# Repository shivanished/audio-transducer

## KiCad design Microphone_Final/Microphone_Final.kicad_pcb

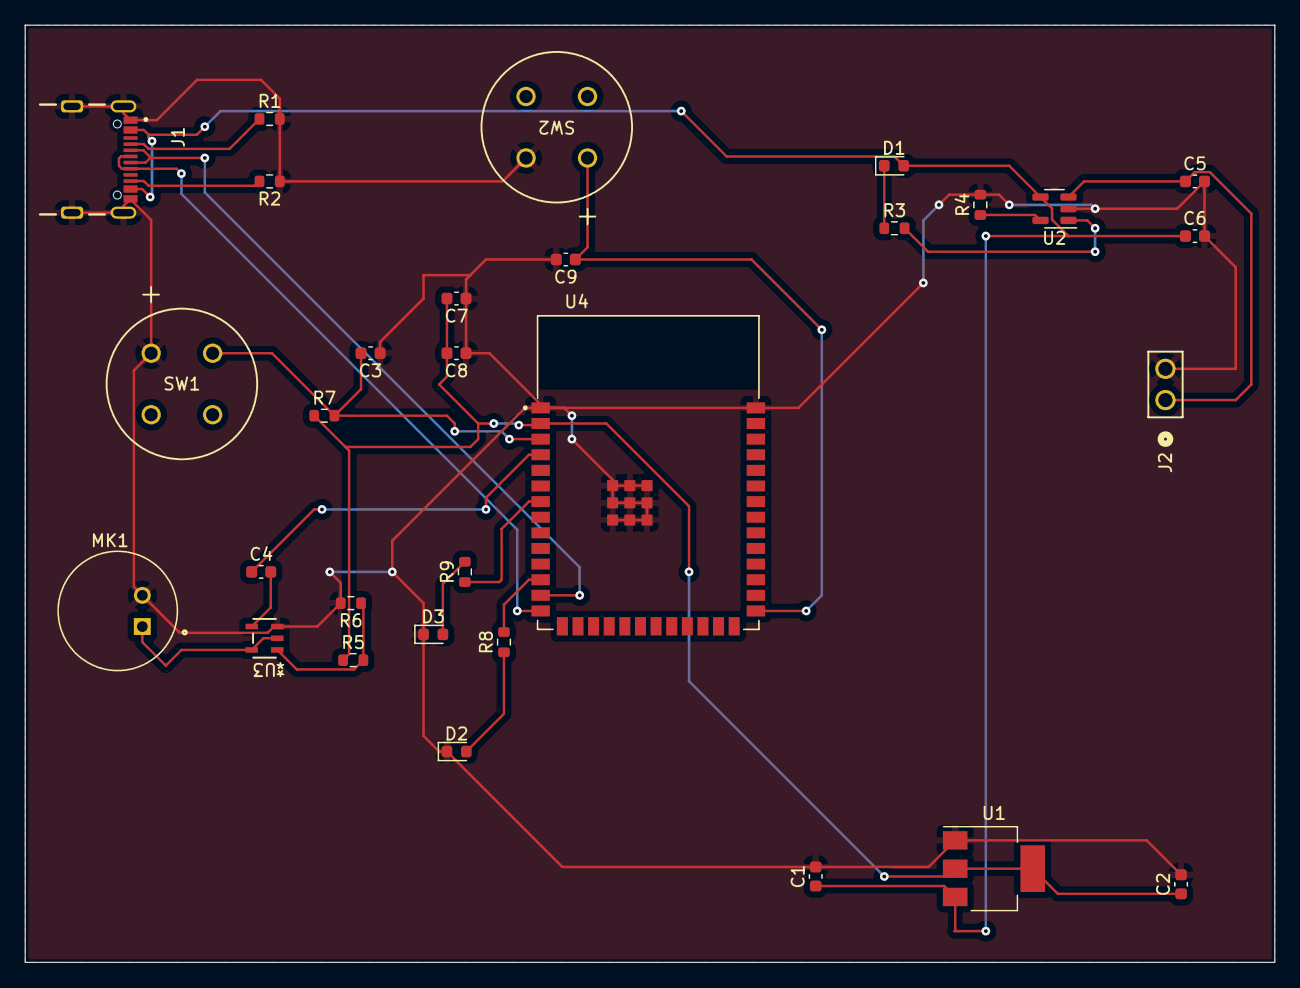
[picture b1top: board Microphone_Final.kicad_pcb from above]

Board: 2 copper layers, 101.6 x 76.2 mm, 30 parts (0 on the bottom side), 21 nets.

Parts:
C1: 100nF; C_0603_1608Metric
C2: 10uF; C_0603_1608Metric
C3, C8, C9: .1uF; C_0603_1608Metric
C4: 1 uF; C_0603_1608Metric
C5, C6: 4.7 uF; C_0603_1608Metric
C7: 1uF; C_0603_1608Metric
D1, D2, D3: LED; LED_0603_1608Metric
J1: USB_C_Receptacle_USB2.0; GCT_USB4105-GF-A
J2: Conn_01x02_Pin; CONN_61300211121_WRE
MK1: Microphone; MIC_CMA-4544PF-W
R1, R2: 5.1 k; R_0603_1608Metric
R3, R8, R9: 470; R_0603_1608Metric
R4: 2000; R_0603_1608Metric
R5: 100; R_0603_1608Metric
R6: 1k; R_0603_1608Metric
R7: 10k; R_0603_1608Metric
SW1: Reset; D6R90_CNK
SW2: Boot; D6R90_CNK
U1: LD1117S33TR_SOT223; SOT-223-3_TabPin2
U2: MCP73831-2-OT; SOT-23-5
U3: ${SIM.PARAMS}; SOT-23-5_MC_MCH-L
U4: ESP32-S2-SOLO; XCVR_ESP32-S2-SOLO-N4

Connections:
+3.3V: C2.1, C7.2, C8.2, R5.1, R7.1, U1.2 (VO), U4.2 (3V3)
+5V: C1.1, C6.1, D1.2 (A), J1.A4_B9, J1.B4_A9, U1.3 (VI), U2.4 (V_{DD})
+BATT: C5.1, J2.1, U2.3 (V_{BAT})
/D+: J1.A6 (D+), J1.B6 (D+), U4.14 (GPIO20/U1CTS/ADC2_CH9/CLK_OUT1/USB_D+)
/D-: J1.A7 (D-), J1.B7 (D-), U4.13 (GPIO19/U1RTS/ADC2_CH8/CLK_OUT2/USB_D-)
GND: C1.2, C2.2, C3.1, C5.2, C6.2, C7.1, C8.1, C9.2, D2.1 (K), D3.1 (K), J1.A1_B12, J1.B1_A12, J1.SH1, J1.SH2, J1.SH3, J1.SH4, J2.2, MK1.2 (+), R1.2, R2.1, R4.2, R6.2, SW1.1, SW2.2, U1.1 (GND), U2.2 (V_{SS}), U3.3 (V+), U4.1 (GND), U4.40 (GND), U4.41_1, U4.41_2, U4.41_3, U4.41_4, U4.41_5, U4.41_6, U4.41_7, U4.41_8, U4.41_9
unnamed: D1.1 (K), R3.1
unnamed: D2.2 (A), R8.1
unnamed: D3.2 (A), R9.2
unnamed: J1.A5 (CC1), R1.1
unnamed: J1.B5 (CC2), R2.2
unnamed: MK1.1 (-), U3.2 (-), U3.5
unnamed: R4.1, U2.5 (PROG)
unnamed: R3.2, U2.1 (STAT)
unnamed: R5.2, R6.1, U3.1 (+)
unnamed: C4.2, U3.4 (V-)
unnamed: C3.2, R7.2, SW1.2, U4.3 (EN)
unnamed: C9.1, SW2.1, U4.27 (GPIO0)
unnamed: C4.1, U4.4 (GPIO4/TOUCH4/ADC1_CH3)
unnamed: R9.1, U4.7 (GPIO7/TOUCH7/ADC1_CH6)
unnamed: R8.2, U4.12 (GPIO8/TOUCH8/ADC1_CH7)

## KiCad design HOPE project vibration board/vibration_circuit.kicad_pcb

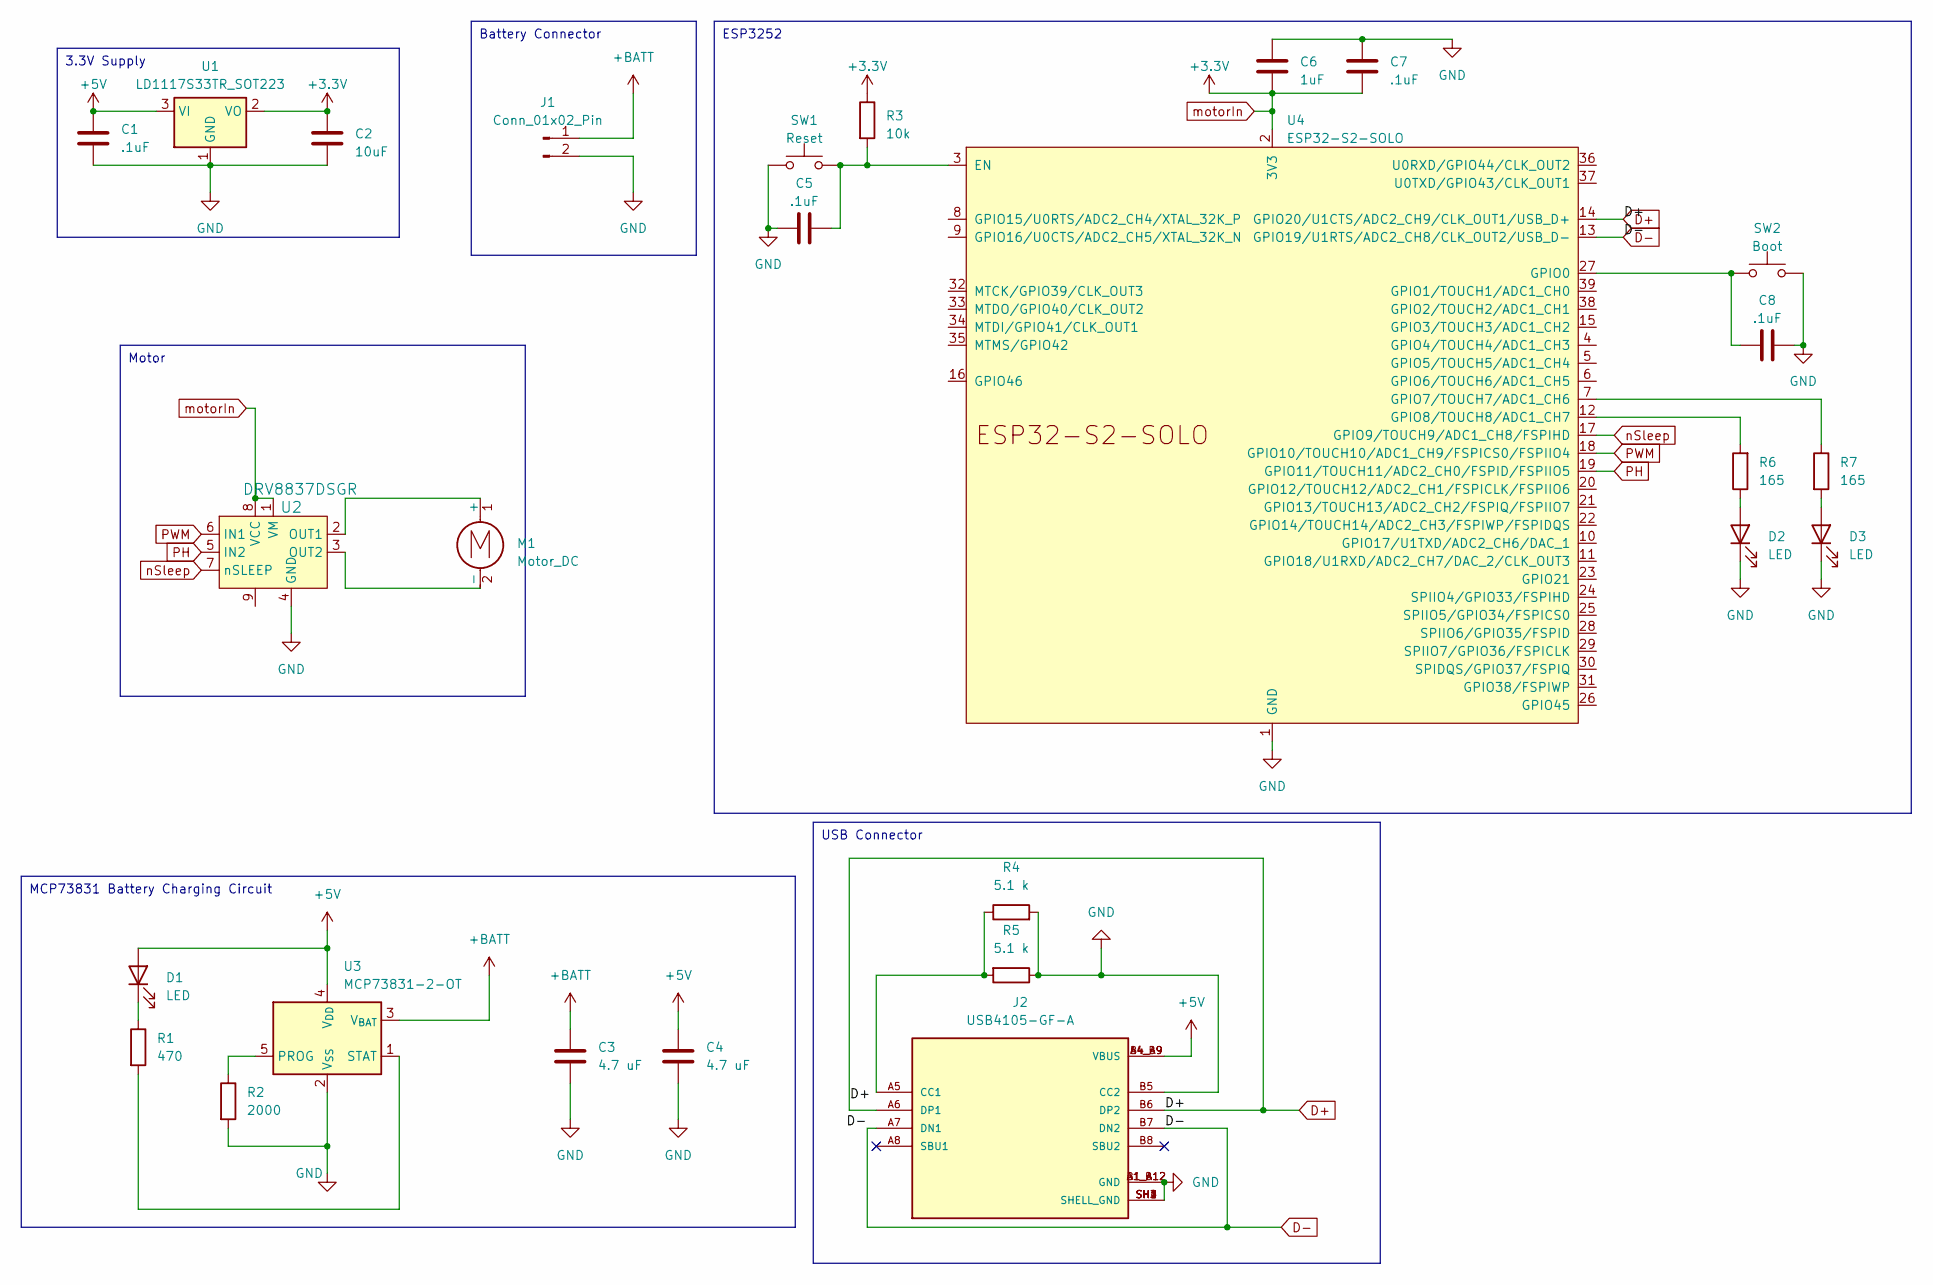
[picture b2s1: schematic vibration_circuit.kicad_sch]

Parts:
C1, C5, C7, C8: .1uF; C_0603_1608Metric
C2: 10uF; C_0603_1608Metric
C3, C4: 4.7 uF; C_0603_1608Metric
C6: 1uF; C_0603_1608Metric
D1, D2, D3: LED; LED_0603_1608Metric
J1: Conn_01x02_Pin; PinSocket_1x02_P2.54mm_Vertical
J2: USB4105-GF-A; GCT_USB4105-GF-A; PARTREV B3
M1: Motor_DC; PinSocket_1x02_P2.54mm_Vertical
R1: 470; R_0603_1608Metric
R2: 2000; R_0603_1608Metric
R3: 10k; R_0805_2012Metric
R4, R5: 5.1 k; R_0603_1608Metric
R6, R7: 165; R_0603_1608Metric
SW1: Reset; SW_JS202011SCQN
SW2: Boot; SW_JS202011SCQN
U1: LD1117S33TR_SOT223; SOT-223-3_TabPin2
U2: DRV8837DSGR; WSON-8-1EP_2x2mm_P0.5mm_EP0.9x1.6mm; MPN DRV8837DSGR; Digi-Key_PN 296-34806-1-ND
U3: MCP73831-2-OT; SOT-23-5
U4: ESP32-S2-SOLO; XCVR_ESP32-S2-SOLO-N4

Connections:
+5V: C1.1, C4.1, D1.2 (A), J2.A4_B9 (VBUS), J2.B4_A9 (VBUS), U1.3 (VI), U3.4 (V_{DD})
+BATT: C3.1, J1.1, U3.3 (V_{BAT})
D+: J2.A6 (DP1), J2.B6 (DP2), U4.14 (GPIO20/U1CTS/ADC2_CH9/CLK_OUT1/USB_D+)
D-: J2.A7 (DN1), J2.B7 (DN2), U4.13 (GPIO19/U1RTS/ADC2_CH8/CLK_OUT2/USB_D-)
GND: C1.2, C2.2, C3.2, C4.2, C5.1, C6.1, C7.1, C8.2, D2.1 (K), D3.1 (K), J1.2, J2.A1_B12 (GND), J2.B1_A12 (GND), J2.B5 (CC2), J2.SH1 (SHELL_GND), J2.SH2 (SHELL_GND), J2.SH3 (SHELL_GND), J2.SH4 (SHELL_GND), R2.2, R4.2, R5.1, SW1.1, SW2.2, U1.1 (GND), U2.4 (GND), U3.2 (V_{SS}), U4.1 (GND), U4.40 (GND), U4.41 (GND)
unnamed: D1.1 (K), R1.1
unnamed: D2.2 (A), R6.1
unnamed: D3.2 (A), R7.2
unnamed: J2.A5 (CC1), R4.1, R5.2
unnamed: M1.1 (+), U2.2 (OUT1)
unnamed: M1.2 (-), U2.3 (OUT2)
unnamed: R2.1, U3.5 (PROG)
unnamed: R1.2, U3.1 (STAT)
unnamed: C5.2, R3.2, SW1.2, U4.3 (EN)
unnamed: C8.1, SW2.1, U4.27 (GPIO0)
unnamed: R7.1, U4.7 (GPIO7/TOUCH7/ADC1_CH6)
unnamed: R6.2, U4.12 (GPIO8/TOUCH8/ADC1_CH7)
PH: U2.5 (IN2), U4.19 (GPIO11/TOUCH11/ADC2_CH0/FSPID/FSPIIO5)
PWM: U2.6 (IN1), U4.18 (GPIO10/TOUCH10/ADC1_CH9/FSPICS0/FSPIIO4)
motorIn: C2.1, C6.2, C7.2, R3.1, U1.2 (VO), U2.1 (VM), U2.8 (VCC), U4.2 (3V3)
nSleep: U2.7 (nSLEEP), U4.17 (GPIO9/TOUCH9/ADC1_CH8/FSPIHD)

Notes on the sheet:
Motor
3.3V Supply
Battery Connector
ESP3252
MCP73831 Battery Charging Circuit
USB Connector

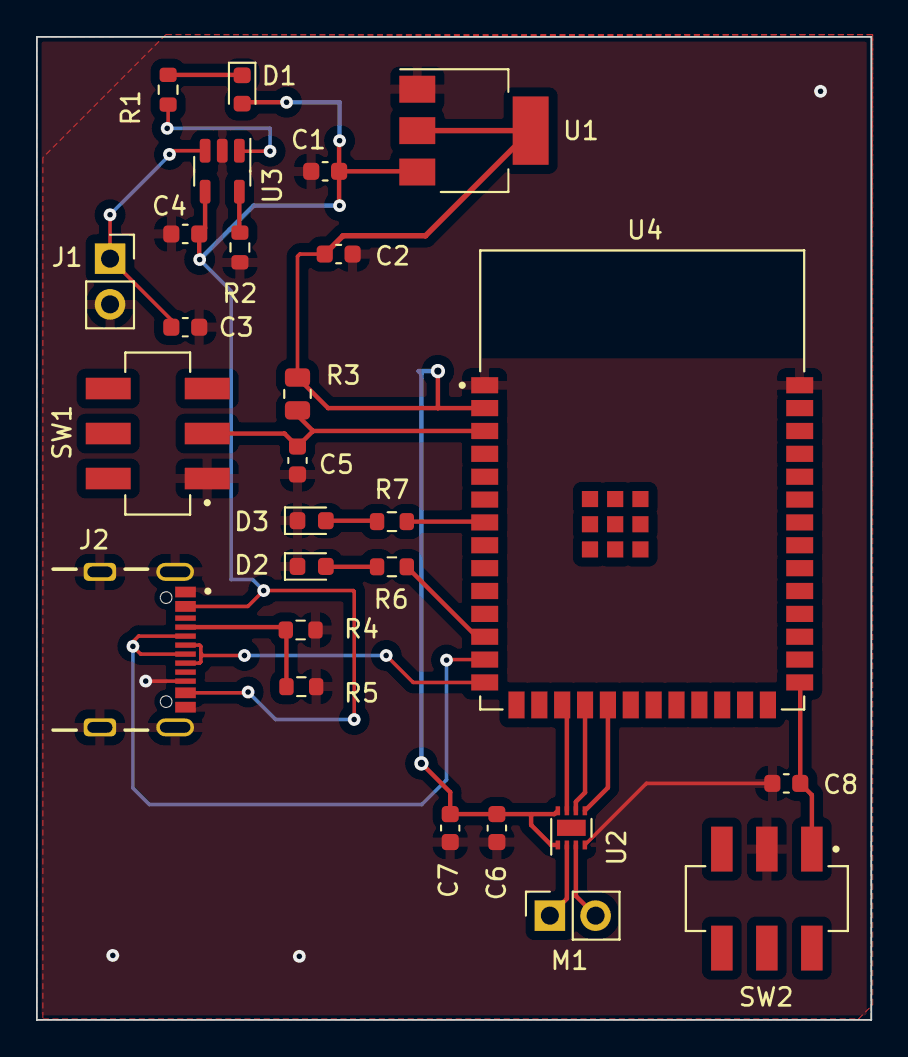
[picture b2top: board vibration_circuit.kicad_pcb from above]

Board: 2 copper layers, 46.4 x 54.6 mm, 27 parts (0 on the bottom side), 21 nets.

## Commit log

2024-04-13 Mic Board and Vibration Board
    Microphone Board and Vibration Board - schematics, layouts, kicad, manufacturing specifications, etc.
